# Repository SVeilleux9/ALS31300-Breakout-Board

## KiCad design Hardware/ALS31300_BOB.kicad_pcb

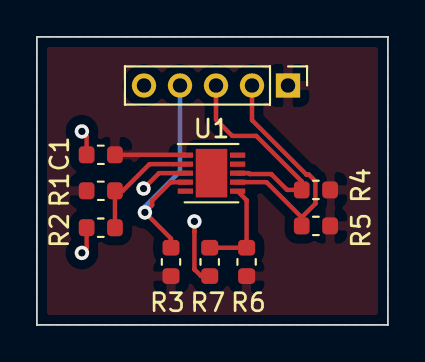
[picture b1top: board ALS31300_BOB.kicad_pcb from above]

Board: 2 copper layers, 19.5 x 16.0 mm, 10 parts (0 on the bottom side), 7 nets.

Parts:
C1: 0.1uF; C_0603_1608Metric
J1: Conn_01x05; PinHeader_1x05_P2.00mm_Vertical
R1, R6: DNP; R_0603_1608Metric
R2, R3, R4, R5, R7: 10k; R_0603_1608Metric
U1: ALS31300; DFN-10-1EP_3x3mm_P0.5mm_EP1.75x2.7mm

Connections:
+3V3: C1.1, J1.1, R1.1, R3.2, R4.1, R5.1, R6.1, U1.1
/INT: J1.4, R3.1, U1.4
/SCL: J1.3, R4.2, U1.8
/SDA: J1.2, R5.2, U1.7
GND: C1.2, J1.5, R2.2, R7.2, U1.3
unnamed: R1.2, R2.1, U1.2
unnamed: R6.2, R7.1, U1.6

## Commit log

2021-11-29 Initial Push
    Contains the break out board and a rough library to communicate with the IC.
2021-11-29 Updated Code
    Pushing the latest version of the code/library.
